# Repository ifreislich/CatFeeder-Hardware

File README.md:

# CatFeeder-Hardware

The control board for the Cat Feeder project.  For completion you will need both
[CatFeeder Firmware](https://github.com/ifreislich/CatFeeder-Firmware)
and
[Catfeeder Enclosure](https://github.com/ifreislich/CatFeeder-3D-Model).

## Wiring
J3 RFID - Wire from HID 5365EGP00 or similar 
Pin|Signal|Wire
---|------|------
1|+12V|Red
2|Data 1|White
3|Data 0|Green
4|GND|Black

J5 Scale - Connection to the Load Cell
Pin|Wire
---|----
1|Black
2|Red
3|Green
4|White

J6 Auger - Nema17 20mm stepper motor
Pin|Signal|Wire
---|------|----
1|2B|Black
2|2A|Green
3|1A|Red
4|1B|Blue

J7 Door - 28BYJ-48 Stepper motor
Pin|Signal|Wire
---|------|----
1|2B|Blue
2|2A|Yellow
3|1A|Pink
4|1B|Orange

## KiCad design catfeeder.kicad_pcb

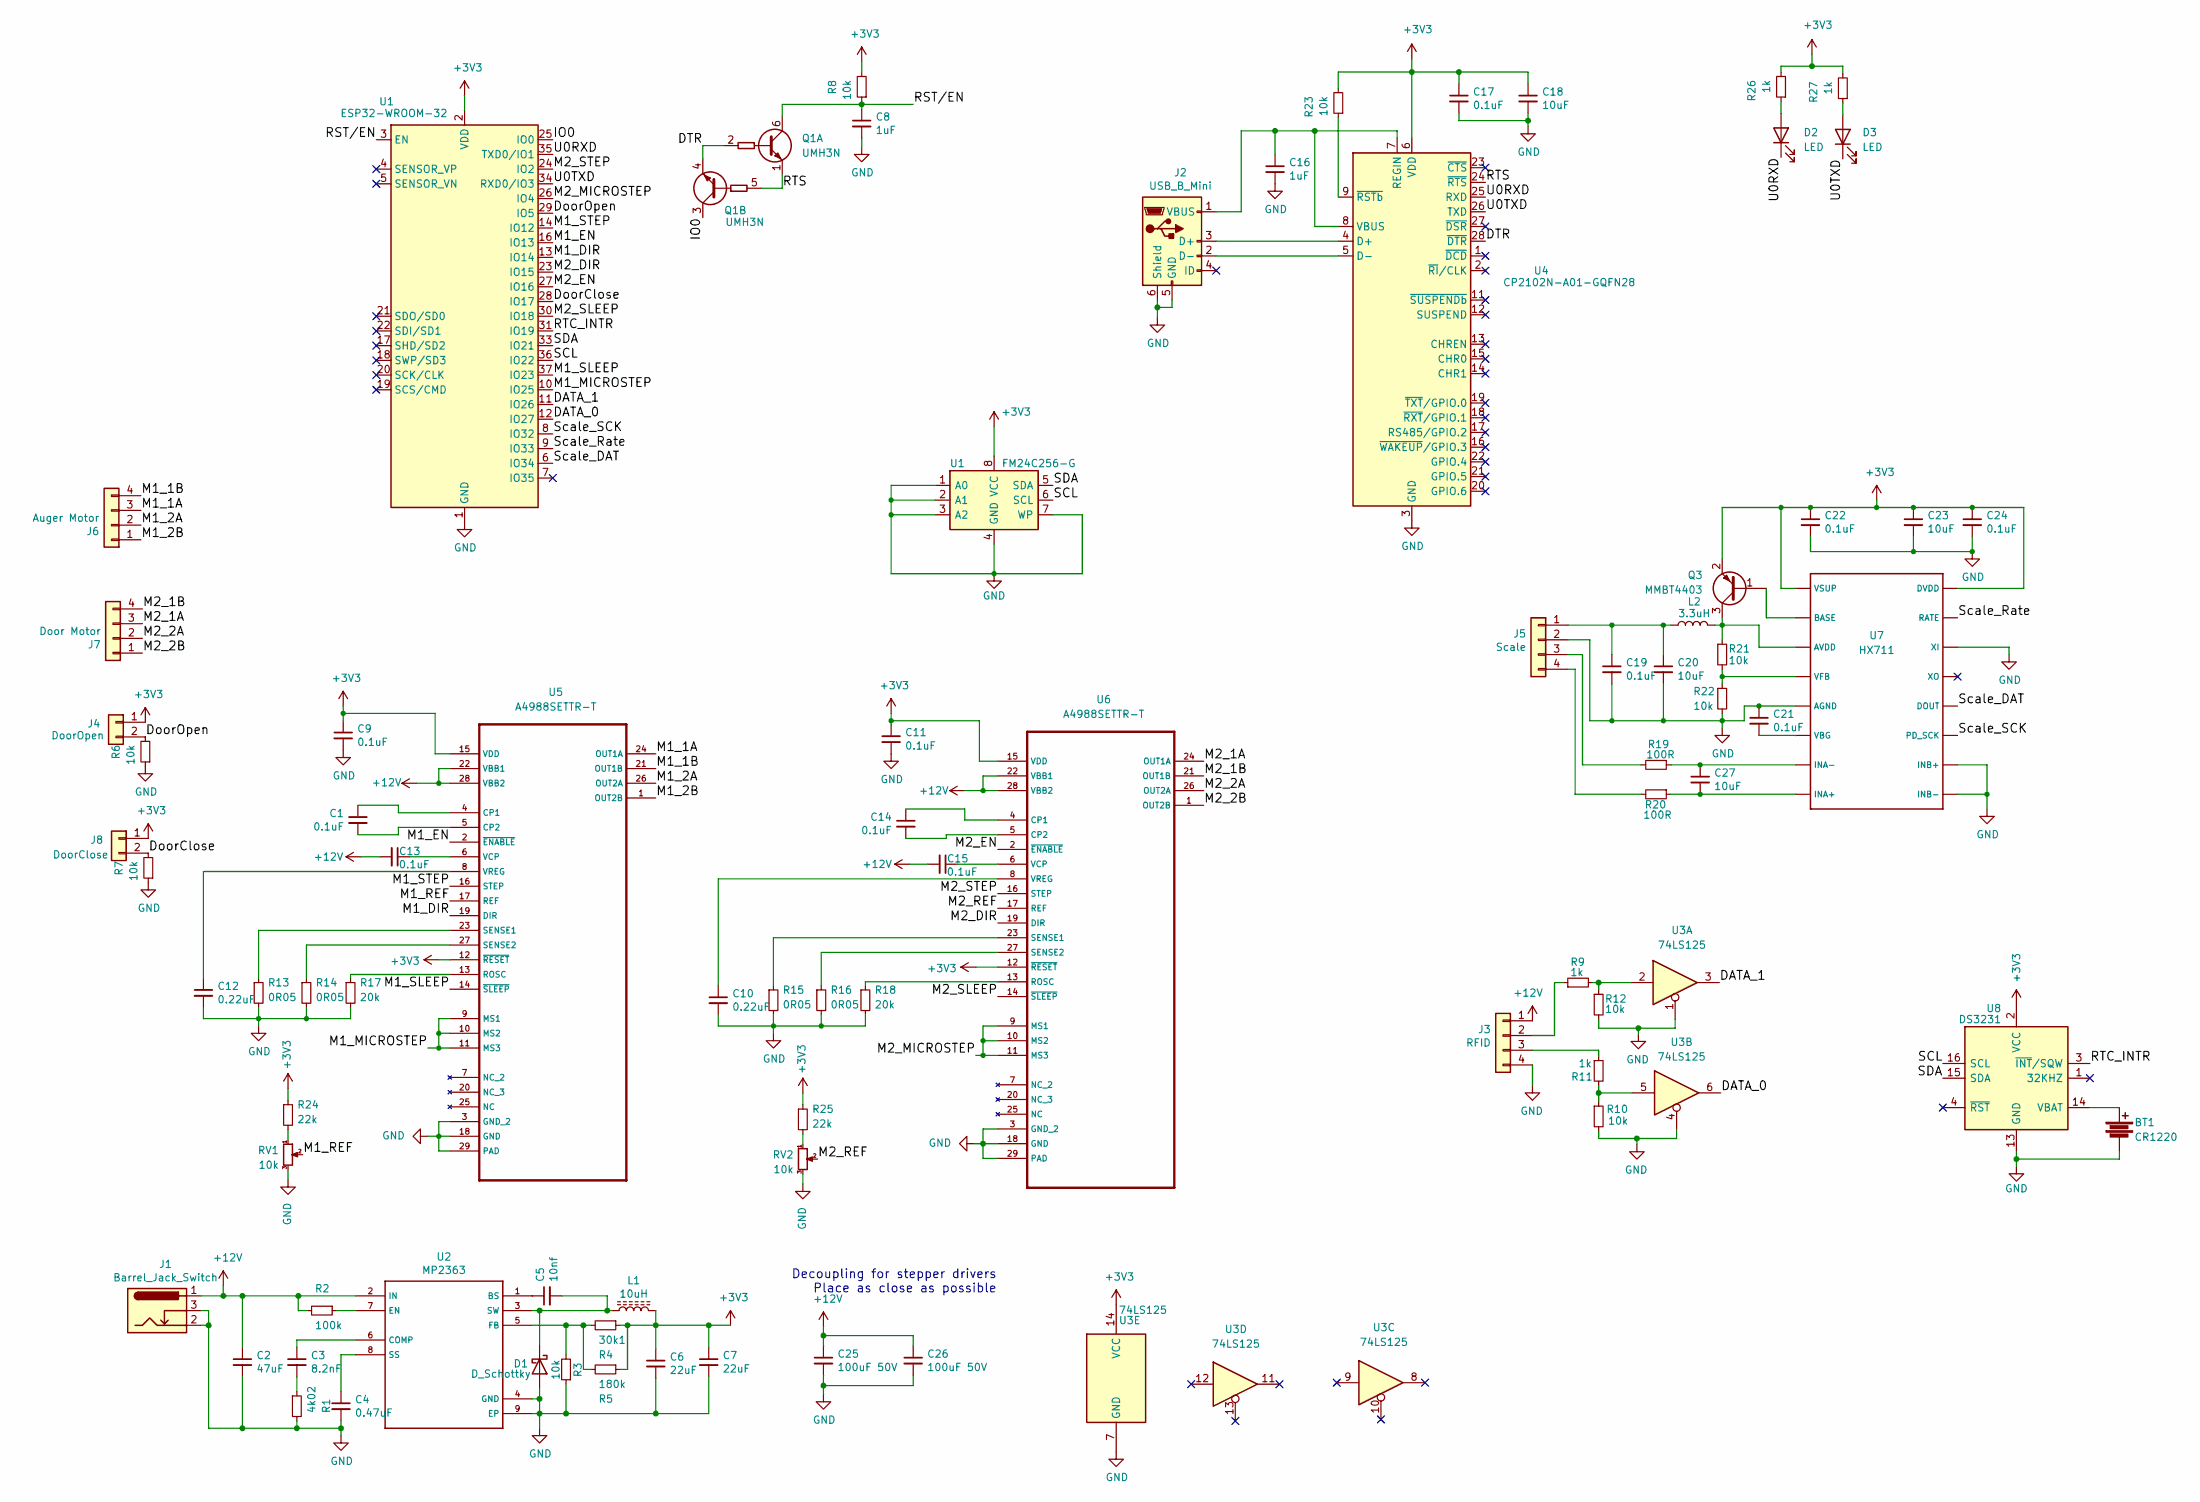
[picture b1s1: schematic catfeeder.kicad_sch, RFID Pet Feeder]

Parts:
BT1: CR1220; CR1220SMD
C1, C9, C11, C13, C14, C15, C17, C19, C21, C22, C24: 0.1uF; C_0603_1608Metric
C2: 47uF; C_1206_3216Metric
C3: 8.2nF; C_0805_2012Metric
C4: 0.47uF; C_0805_2012Metric
C5: 10nf; C_0805_2012Metric
C6, C7: 22uF; C_0805_2012Metric
C8: 1uF; C_0603_1608Metric
C10, C12: 0.22uF; C_0805_2012Metric
C16: 1uF; C_0805_2012Metric
C18, C20, C23: 10uF; C_0805_2012Metric
C25, C26: 100uF 50V; C_1210_3225Metric
C27: 10uF; C_0603_1608Metric
D1: D_Schottky; D_SMA
D2, D3: LED; LED_0805_2012Metric
J1: Barrel_Jack_Switch; BarrelJack_Horizontal
J2: USB_B_Mini; USB_Mini-B_Lumberg_2486_01_Horizontal
J3: RFID; JST_PH_B4B-PH-K_1x04_P2.00mm_Vertical
J4: DoorOpen; JST_PH_B2B-PH-K_1x02_P2.00mm_Vertical
J5: Scale; JST_PH_B4B-PH-K_1x04_P2.00mm_Vertical
J6: Auger Motor; JST_PH_B4B-PH-K_1x04_P2.00mm_Vertical
J7: Door Motor; JST_PH_B4B-PH-K_1x04_P2.00mm_Vertical
J8: DoorClose; JST_PH_B2B-PH-K_1x02_P2.00mm_Vertical
L1: 10uH; L_7.3x7.3_H3.5
L2: 3.3uH; L_0805_2012Metric
Q1: UMH3N; SOT-363_SC-70-6
Q3: MMBT4403; SOT-23
R1: 4k02; R_0603_1608Metric
R2: 100k; R_0603_1608Metric
R3, R6, R7, R8, R10, R12, R21, R22, R23: 10k; R_0603_1608Metric
R4: 30k1; R_0805_2012Metric
R5: 180k; R_0805_2012Metric
R9, R11, R26, R27: 1k; R_0603_1608Metric
R13, R14, R15, R16: 0R05; R_0603_1608Metric
R17, R18: 20k; R_0603_1608Metric
R19, R20: 100R; R_0603_1608Metric
R24, R25: 22k; R_0805_2012Metric
RV1, RV2: 10k; Potentiometer_Bourns_TC33X_Vertical
U1: ESP32-WROOM-32
U2: MP2363; HSOP-8-1EP_3.9x4.9mm_P1.27mm_EP2.41x3.1mm_ThermalVias
U3: 74LS125; SOIC-14_3.9x8.7mm_P1.27mm
U4: CP2102N-A01-GQFN28; QFN-28-1EP_5x5mm_P0.5mm_EP3.35x3.35mm_ThermalVias
U5, U6: A4988SETTR-T; QFN-28-1EP_5x5mm_P0.5mm_EP3.35x3.35mm_ThermalVias
U7: HX711; SO-16_3.9x9.9mm_P1.27mm
U8: DS3231; SOIC-16W_7.5x10.3mm_P1.27mm

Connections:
+12V: C2.1, C13.2, C15.2, C25.1, C26.1, J1.1, J3.1, R2.2, U2.2 (IN), U5.22 (VBB1), U5.28 (VBB2), U6.22 (VBB1), U6.28 (VBB2)
/DATA_0: U1.12 (IO27), U3.6
/DATA_1: U1.11 (IO26), U3.3
/DTR: Q1.2 (B1), Q1.4 (E2), U4.28 (~DTR)
/DoorClose: J8.2, R7.2, U1.28 (IO17)
/DoorOpen: J4.2, R6.2, U1.29 (IO5)
/IO0: Q1.3 (C2), U1.25 (IO0)
/M1_1A: J6.3, U5.24 (OUT1A)
/M1_1B: J6.4, U5.21 (OUT1B)
/M1_2A: J6.2, U5.26 (OUT2A)
/M1_2B: J6.1, U5.1 (OUT2B)
/M1_DIR: U1.13 (IO14), U5.19 (DIR)
/M1_EN: U1.16 (IO13), U5.2 (~ENABLE)
/M1_MICROSTEP: U1.10 (IO25), U5.9 (MS1), U5.10 (MS2), U5.11 (MS3)
/M1_REF: RV1.2, U5.17 (REF)
/M1_SLEEP: U1.37 (IO23), U5.14 (~SLEEP)
/M1_STEP: U1.14 (IO12), U5.16 (STEP)
/M2_1A: J7.3, U6.24 (OUT1A)
/M2_1B: J7.4, U6.21 (OUT1B)
/M2_2A: J7.2, U6.26 (OUT2A)
/M2_2B: J7.1, U6.1 (OUT2B)
/M2_DIR: U1.23 (IO15), U6.19 (DIR)
/M2_EN: U1.27 (IO16), U6.2 (~ENABLE)
/M2_MICROSTEP: U1.26 (IO4), U6.9 (MS1), U6.10 (MS2), U6.11 (MS3)
/M2_REF: RV2.2, U6.17 (REF)
/M2_SLEEP: U1.30 (IO18), U6.14 (~SLEEP)
/M2_STEP: U1.24 (IO2), U6.16 (STEP)
/RTC_INTR: U1.31 (IO19), U8.3 (~INT/SQW)
/RTS: Q1.1 (E1), Q1.5 (B2), U4.24 (~RTS)
/SDA: U1.5 (SDA), U1.33 (IO21), U8.15 (SDA); also elsewhere on the board
/Scale_Rate: U1.9 (IO33), U7.15 (RATE)
/U0RXD: D2.1 (K), U1.35 (TXD0/IO1), U4.25 (RXD)
/U0TXD: D3.1 (K), U1.34 (RXD0/IO3), U4.26 (TXD)
unnamed: C3.2, R1.1
unnamed: C5.2, D1.1 (K), L1.1, U2.3 (SW)
unnamed: D2.2 (A), R26.1
unnamed: D3.2 (A), R27.1
unnamed: J2.3 (D+), U4.4 (D+)
unnamed: J2.2 (D-), U4.5 (D-)
unnamed: C16.1, J2.1 (VBUS), U4.7 (REGIN), U4.8 (VBUS)
unnamed: J3.2, R9.1
unnamed: J3.3, R11.1
unnamed: C19.1, C20.1, J5.1, L2.1
unnamed: J5.3, R19.2
unnamed: J5.4, R20.2
unnamed: Q3.1 (B), U7.2 (BASE)
unnamed: L2.2, Q3.3 (C), R21.1, U7.3 (AVDD)
unnamed: R10.1, R11.2, U3.5
unnamed: R9.2, R12.1, U3.2
unnamed: R24.2, RV1.1
unnamed: R25.2, RV2.1
unnamed: C5.1, U2.1 (BS)
unnamed: C3.1, U2.6 (COMP)
unnamed: R2.1, U2.7 (EN)
unnamed: R3.2, R4.2, R5.2, U2.5 (FB)
unnamed: C4.1, U2.8 (SS)
unnamed: R23.1, U4.9 (~RSTb)
unnamed: C1.1, U5.4 (CP1)
unnamed: C1.2, U5.5 (CP2)
unnamed: R17.1, U5.13 (ROSC)
unnamed: R13.1, U5.23 (SENSE1)
unnamed: R14.1, U5.27 (SENSE2)
unnamed: C13.1, U5.6 (VCP)
unnamed: C12.1, U5.8 (VREG)
unnamed: C14.1, U6.4 (CP1)
unnamed: C14.2, U6.5 (CP2)
unnamed: R18.1, U6.13 (ROSC)
unnamed: R15.1, U6.23 (SENSE1)
unnamed: R16.1, U6.27 (SENSE2)
unnamed: C15.1, U6.6 (VCP)
unnamed: C10.1, U6.8 (VREG)
unnamed: C27.2, R20.1, U7.8 (INA+)
unnamed: C27.1, R19.1, U7.7 (INA-)
unnamed: C21.2, U7.6 (VBG)
unnamed: R21.2, R22.1, U7.4 (VFB)
unnamed: BT1.1, U8.14 (VBAT)

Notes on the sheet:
Decoupling for stepper drivers Place as close as possible

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
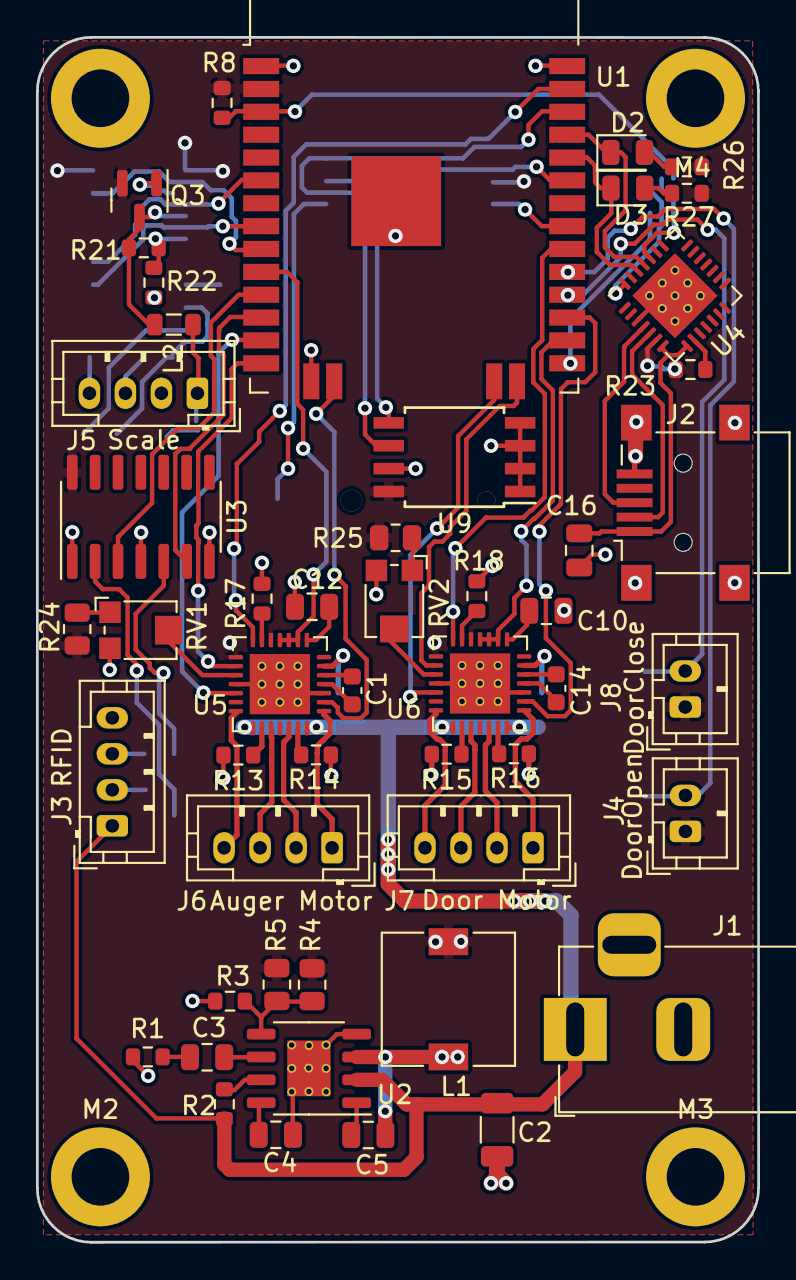
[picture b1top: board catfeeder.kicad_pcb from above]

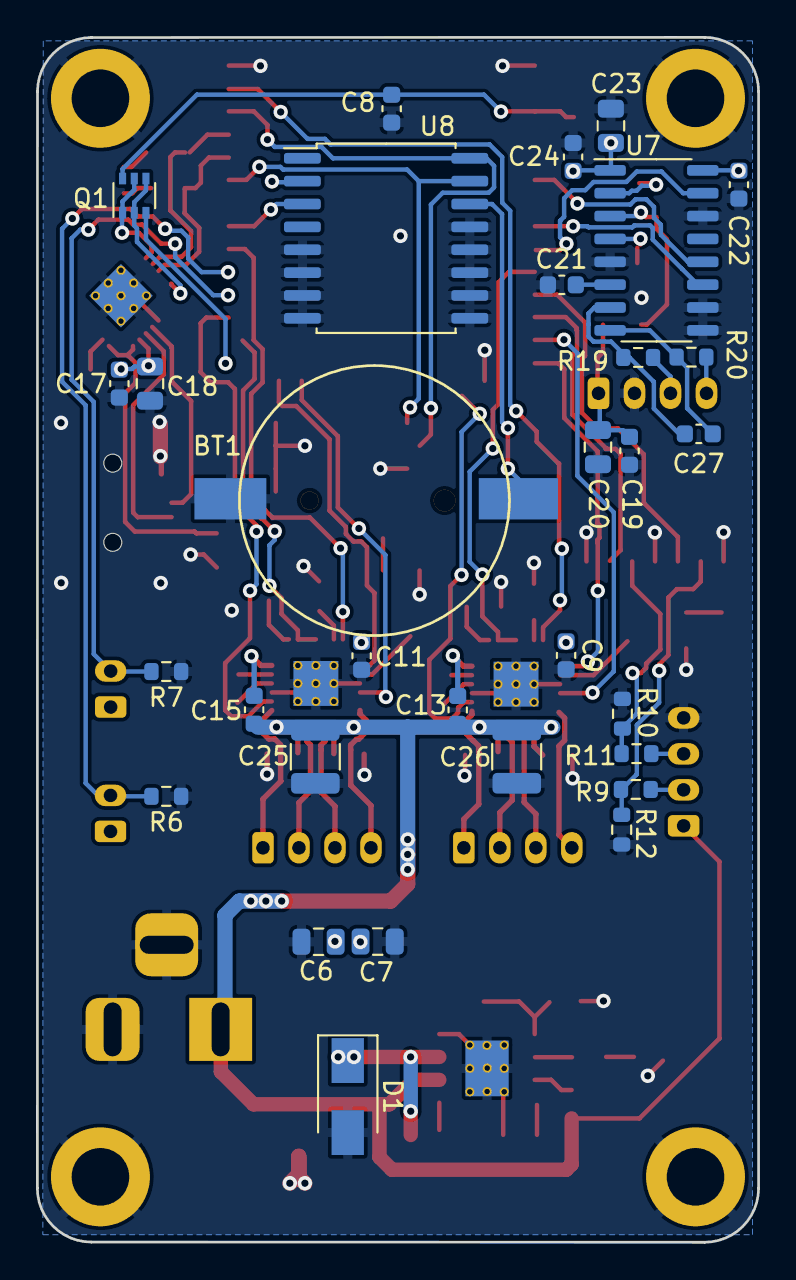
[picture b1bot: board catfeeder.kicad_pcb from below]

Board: 2 copper layers, 40.1 x 66.9 mm, 85 parts (31 on the bottom side), 82 nets.

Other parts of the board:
M1, M2, M3, M4: Mount; MountingHole_3.2mm_M3_ISO14580_Pad
U9: FM24C256-G; SOIC-8W_5.3x5.3mm_P1.27mm

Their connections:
/SDA: U9.5 (SDA); also elsewhere on the board

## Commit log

2023-06-28 Add the license
2023-07-12 Add renders of the board front and back.
2023-07-12 Cleanup tracks and vias.
2023-07-14 Add a PDF of the schematic
2023-07-14 Update the page title and revision.
2023-08-21 Save with new KiCAD version. Cleanup some tracks and vias.
2023-08-22 Update the model for the barrel jack.
2023-08-22 Re-generate the image because one of the connectors was highlighted.
2023-08-22 Regenerate again to remove the connector highlight.
